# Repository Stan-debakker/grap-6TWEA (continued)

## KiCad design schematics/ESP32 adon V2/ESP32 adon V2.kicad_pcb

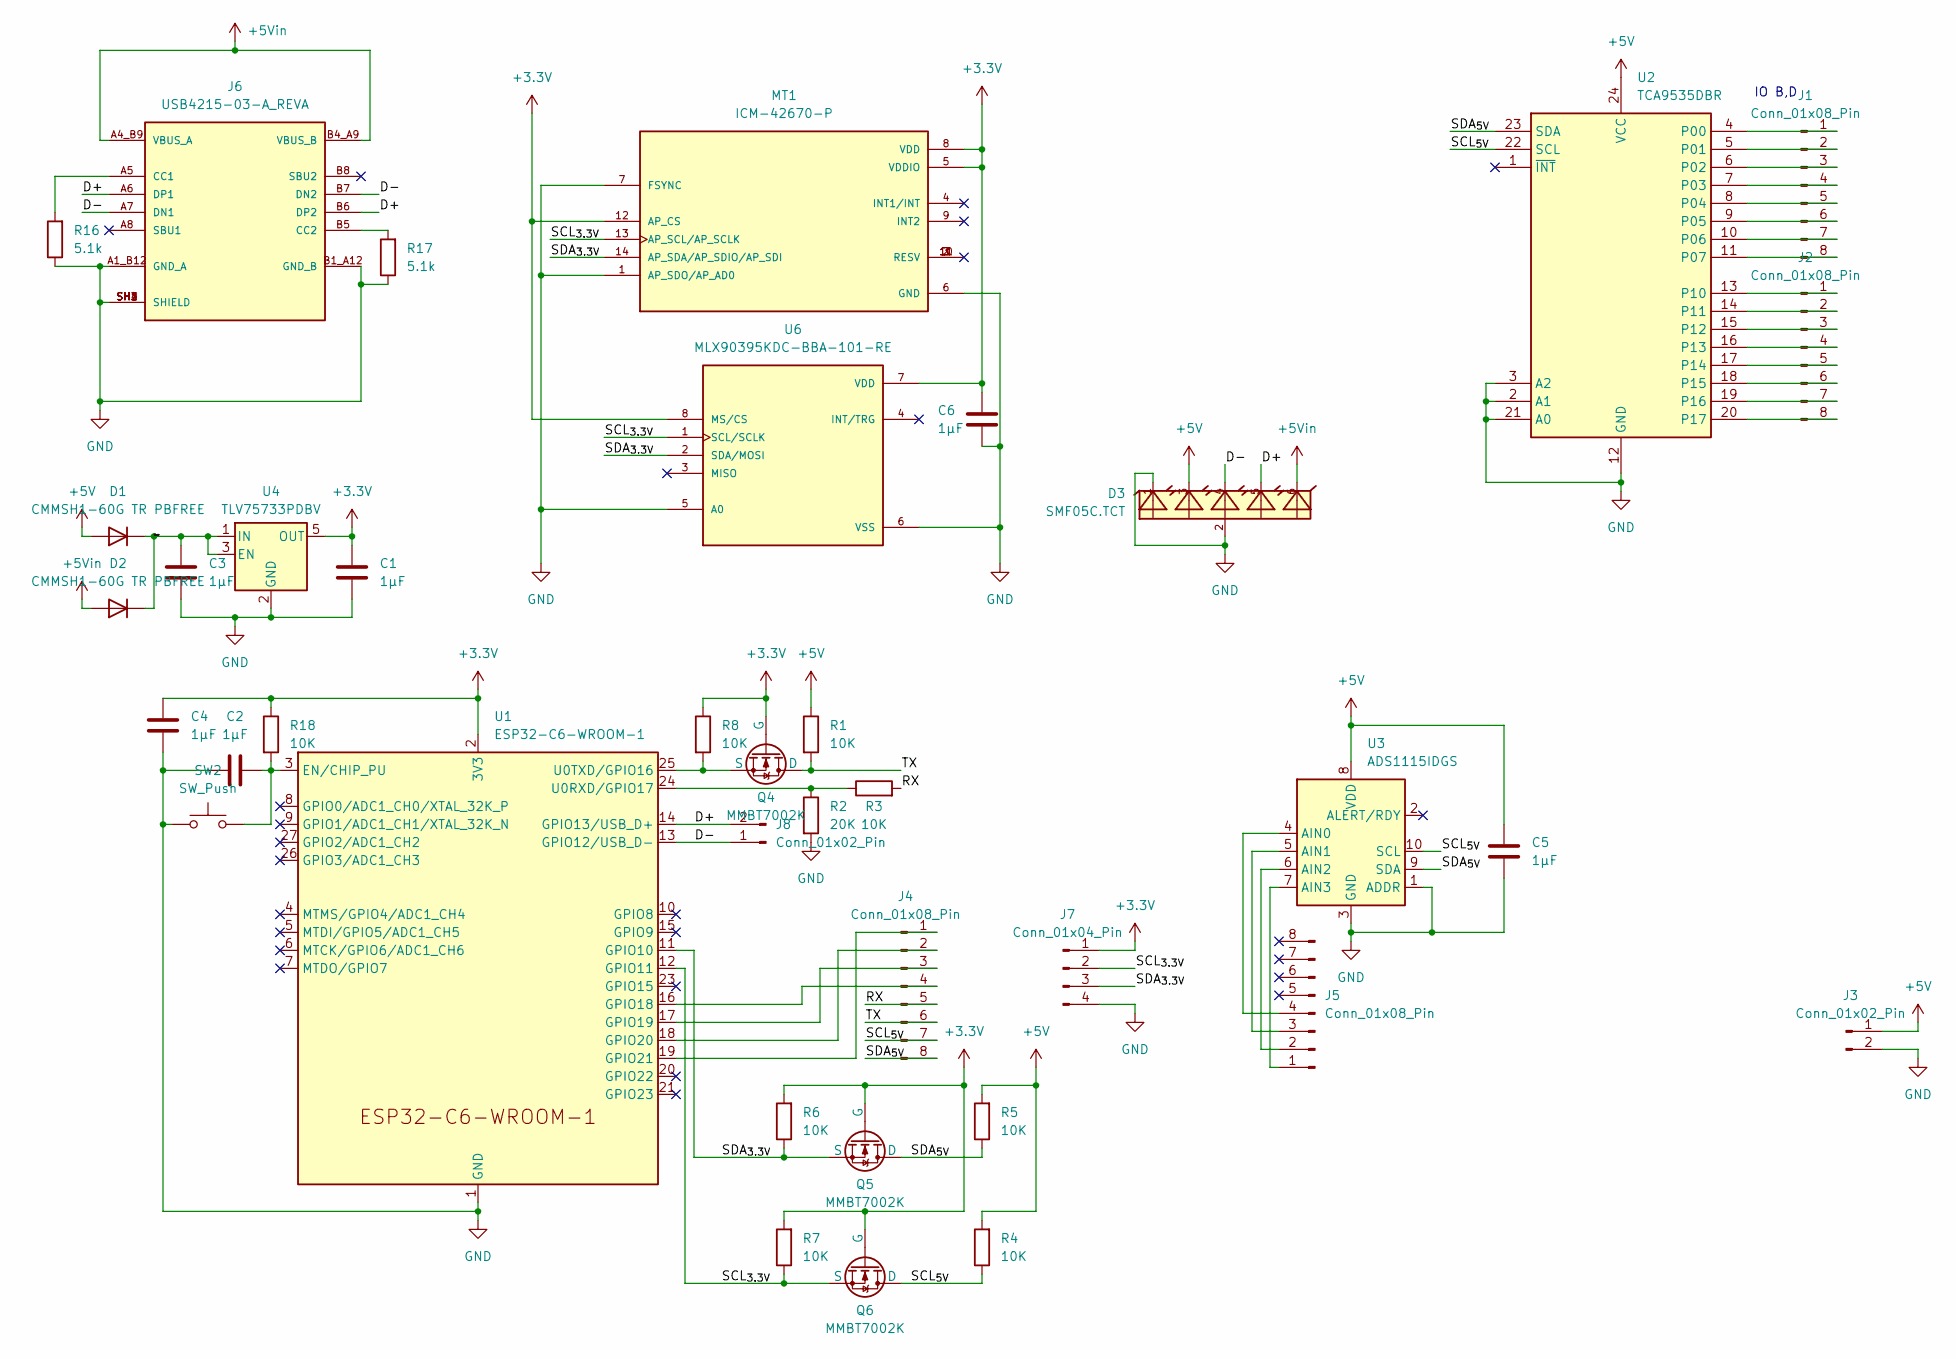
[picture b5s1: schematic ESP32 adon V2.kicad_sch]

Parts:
C1, C2, C3, C4, C5, C6: 1µF; C_0603_1608Metric
D1, D2: CMMSH1-60G TR PBFREE; D_SOD-123F
D3: SMF05C.TCT; Vishay_PowerPAK_SC70-6L_Dual
J1, J2, J4, J5: Conn_01x08_Pin; PinSocket_1x08_P2.54mm_Vertical
J3: Conn_01x02_Pin; PinSocket_1x02_P2.54mm_Vertical
J6: USB4215-03-A_REVA; usb4215-3472997; PARTREV A
J7: Conn_01x04_Pin; PinSocket_1x04_P2.54mm_Vertical
J8: Conn_01x02_Pin; R_0603_1608Metric_Pad0.98x0.95mm_HandSolder
MT1: ICM-42670-P; Bosch_LGA-14_3x2.5mm_P0.5mm; PARTREV 1.1
Q4, Q5, Q6: MMBT7002K; SOT-23
R1, R3, R4, R5, R6, R7, R8, R18: 10K; R_0603_1608Metric
R2: 20K; R_0603_1608Metric
R16, R17: 5.1k; R_0603_1608Metric
SW2: SW_Push; SW_PUSH_6mm
U1: ESP32-C6-WROOM-1
U2: TCA9535DBR; TSSOP-24_4.4x7.8mm_P0.65mm
U3: ADS1115IDGS; TSSOP-10_3x3mm_P0.5mm
U4: TLV75733PDBV; SOT-23-5
U6: MLX90395KDC-BBA-101-RE; SOIC-8_3.9x4.9mm_P1.27mm; PARTREV 6.0

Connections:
+3.3V: C1.1, C4.2, C6.2, J7.1, MT1.5 (VDDIO), MT1.8 (VDD), MT1.12 (AP_CS), Q4.2 (G), Q5.2 (G), Q6.2 (G), R6.2, R7.2, R8.1, R18.1, U1.2 (3V3), U4.5 (OUT), U6.7 (VDD), U6.8 (MS/CS)
+5V: C5.2, D1.2 (A), D3.3, J3.1, R1.1, R4.2, R5.2, U2.24 (VCC), U3.8 (VDD)
+5Vin: D2.2 (A), D3.6, J6.A4_B9 (VBUS_A), J6.B4_A9 (VBUS_B)
/D+: D3.5, J6.A6 (DP1), J6.B6 (DP2), J8.2, U1.14 (GPIO13/USB_D+)
/D-: D3.4, J6.A7 (DN1), J6.B7 (DN2), J8.1, U1.13 (GPIO12/USB_D-)
/RX: J4.5, R3.2
/SCL_{3.3V}: J7.2, MT1.13 (AP_SCL/AP_SCLK), Q6.3 (S), R7.1, U1.12 (GPIO11), U6.1 (SCL/SCLK)
/SCL_{5V}: J4.7, Q6.1 (D), R4.1, U2.22 (SCL), U3.10 (SCL)
/SDA_{3.3V}: J7.3, MT1.14 (AP_SDA/AP_SDIO/AP_SDI), Q5.3 (S), R6.1, U1.11 (GPIO10), U6.2 (SDA/MOSI)
/SDA_{5V}: J4.8, Q5.1 (D), R5.1, U2.23 (SDA), U3.9 (SDA)
/TX: J4.6, Q4.1 (D), R1.2
/Vin_reg: C3.1, D1.1 (K), D2.1 (K), U4.1 (IN), U4.3 (EN)
unnamed: J1.1, U2.4 (P00)
unnamed: J1.2, U2.5 (P01)
unnamed: J1.3, U2.6 (P02)
unnamed: J1.4, U2.7 (P03)
unnamed: J1.5, U2.8 (P04)
unnamed: J1.6, U2.9 (P05)
unnamed: J1.7, U2.10 (P06)
unnamed: J1.8, U2.11 (P07)
unnamed: J2.1, U2.13 (P10)
unnamed: J2.2, U2.14 (P11)
unnamed: J2.3, U2.15 (P12)
unnamed: J2.4, U2.16 (P13)
unnamed: J2.5, U2.17 (P14)
unnamed: J2.6, U2.18 (P15)
unnamed: J2.7, U2.19 (P16)
unnamed: J2.8, U2.20 (P17)
unnamed: J4.1, U1.19 (GPIO21)
unnamed: J4.2, U1.18 (GPIO20)
unnamed: J4.3, U1.17 (GPIO19)
unnamed: J4.4, U1.16 (GPIO18)
unnamed: J5.1, U3.7 (AIN3)
unnamed: J5.2, U3.6 (AIN2)
unnamed: J5.3, U3.5 (AIN1)
unnamed: J5.4, U3.4 (AIN0)
unnamed: J6.A5 (CC1), R16.2
unnamed: J6.B5 (CC2), R17.2
unnamed: Q4.3 (S), R8.2, U1.25 (U0TXD/GPIO16)
unnamed: C2.2, R18.2, SW2.2, U1.3 (EN/CHIP_PU)
unnamed: R2.1, R3.1, U1.24 (U0RXD/GPIO17)

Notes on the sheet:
IO B,D

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
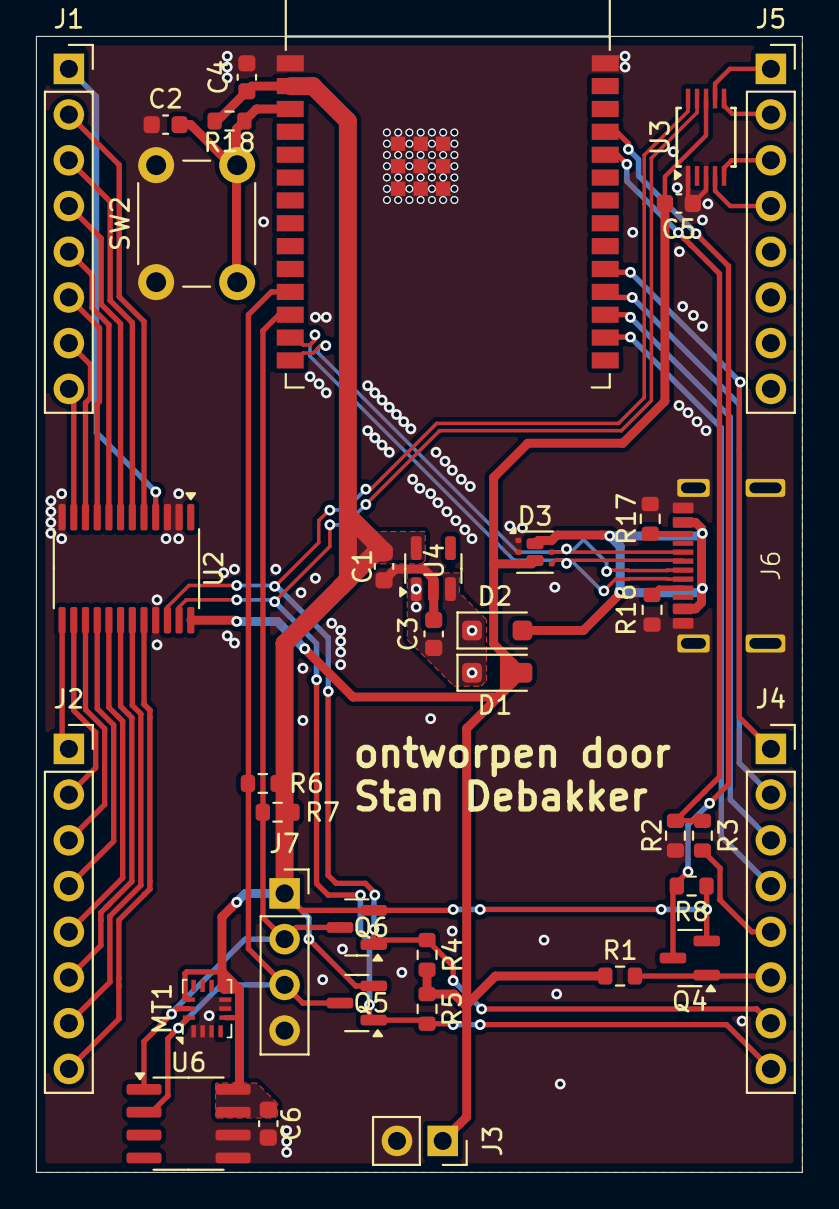
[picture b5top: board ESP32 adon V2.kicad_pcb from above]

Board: 2 copper layers, 42.5 x 63.1 mm, 38 parts (1 on the bottom side), 42 nets.

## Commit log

2025-03-07 voeg de al gemaakte bestanden toe
2025-03-08 verbeterde pcb layout
2025-03-08 voeg de berekeningen toe voor de VIA's
2025-03-08 voeg de voor school verplichte opdrachten toe
2025-03-08 voeg de foto en code om die beter te maken toe
2025-03-08 bug uit code gehaald waardoor het niet update
2025-03-09 kleine update afische
2025-03-09 voeg de word versie van studie 2 toe
2025-03-09 verander de naam van studie_1.pdf naar studie 1.pdf
2025-03-10 voeg de versie volgens mijn mama toe
2025-03-10 afische verbeterd
2025-03-10 de bijna defenitieve versie van de robot
2025-03-10 de finale versie van het afiche
2025-03-11 voeg de exel voor de taak 50% toe
2025-03-11 bijna alle vragen van de taak 50% zijn ingevuld
2025-03-12 voeg de STM32 cubeIDE bestanden (onafgewerkt) toe
2025-03-12 kleine aanpasing om op een arduino Mega te werken
2025-03-12 nutteloze map verwijderd
2025-03-12 voeg .metadata/ toe aan .gitignore om hem niet opte slaan
2025-03-13 update het afiche met de comentaar die ik kreeg
2025-03-13 kleine update van lijnsensor schema
2025-03-17 schema geupdate voor ATtiny 202 (nog niet af)
2025-03-17 schema bijna klaar allen nog SRF02 toevoegen
2025-03-18 wek '50%' voledig af
2025-03-18 hoofdschema is af
2025-03-18 veranert de ATtiny202 naat ATtiny402 om genoeg opslag te hebben
2025-03-18 verwijder code_STM32_cubeIDE omdat ik geen STM32 meer ga gebruiken wan de app deet te ambetand en ik hem niet strict nodig hebben
2025-03-18 voeg de lichtsensor toe aan het hoofd
2025-03-18 .gitignore geupdate zodat de 'nutteloze' bestanden niet worden opgeladen
2025-03-20 teken de outline van het hoofd, en plaats de SRF02 (locatie gevoelig)
2025-03-20 teken de outline van lijnsensor bord + conector positionering
2025-03-21 plaats de componenten grofweg
2025-03-21 voeg de ontbrekende foodprints toe
2025-03-21 teken alles waarvan ik de locate ken of niet belangrijk is (absolut)
2025-03-21 led van het 'mondje' zijn geplaatst
2025-03-21 de locatie van alle componenten is bepaald in het hoofd
2025-03-22 nieuw hoofd is klaar
2025-03-22 ESD bescherming voor de lijnsensor
2025-03-23 de routing is klaar van de lijnsensor nog allen opschonen
2025-03-23 lijnsensor is klaar
2025-03-23 voeg de gaten toe om te kunnen vastvijzen
2025-03-23 maak de gbr file's voor nieuw hoofd
2025-03-23 maak de gbr file's voor lijnsensor
2025-03-23 maak de gbr file's voor ESP32 adon V2
2025-03-29 niewe code voor de ADC geschreven
2025-04-12 voeg todo.txt toe
2025-04-14 IMU.ino en machnetometer.ino werken
2025-04-22 dupliceer de huidige bestanden en voeg de pullup weerstand toe
2025-04-22 verwijder de *.zip bestanden
2025-04-22 update de schematics
2025-04-22 teken al een deel van de lijnsensor
2025-04-24 begin al met het tekenen van ESP32 addon V3
2025-04-24 verder tekenen en datasheets controleren
2025-04-26 voeg de imu en de 3.3V I²C conectoren toe
2025-04-26 zet alle componenten op de juist plaats en alles is al verbonden
2025-04-26 heatsikn voor de ESP32 maken
2025-04-26 voeg het exel document toe waar de via's moeten komen
2025-04-27 controller ESP32 addon V3
2025-04-28 maak een pdf om aftedrukken om te weten als alles goed is
2025-04-28 zet alles op de juiste plaats
2025-04-28 updata alle afmetingen en maak er een pdf van
2025-04-28 teken al wat van het nieuw hoofd
2025-04-29 zet de leds en lichtsensoren op de juisteplaats nieuw hoofd V2
2025-04-29 nieuw hoofd V2 is klaar
2025-04-29 voeg meer via's toe
2025-05-01 klaar met lijnsensor V2
2025-05-01 voeg mijn naam toe aan nieuw hoofd en lijnsensor
2025-05-02 update de .gitignore en voeg viea's toe aan ESP32 addon V3
2025-05-02 verander het I²C adders van de I²C multiplexer om conflict te vermijden
2025-05-02 maak een versie van de lijnsensor die alle pinnen van de lichtsenser gebruikt
2025-05-04 begin al met het toevoegen van de io extender nog niet klaar
2025-05-05 pas de maten aan van de addon V3 en de lijnsensor(nog niet klaar)
2025-05-05 voeg 75%.xlsx toe en vul het al gedeeltelijk in
2025-05-05 de linker kant is al klaar nu nog de rechter kant van lijnsensor V2 met IO_expander
2025-05-05 al begonnen aan de rechterkand van lijnsensor V2 met IO_expander
2025-05-05 klaar met het tekenen van alle verbindingen en veel via's geplaatst
2025-05-06 alles is nagemeten en 75% is ingeleverd
2025-05-06 maak de .gbr bestanden
2025-05-07 maak nieuw hoofd maar met een andere sensorn want de originele is niet meer beschikbaar in kleine hoeveeldheden
2025-05-08 voeg nog ESD bescherming toe aan nieuw hoofd V3
2025-05-09 zorg dat de .gbr files van nieuw hoofd V3 juist zijn
2025-05-11 maak de basis van de eindprisentatie
2025-05-13 voeg iets toe aan todo.txt
2025-05-13 de f.paste layer is goed
2025-05-13 verwijder de oude bestanden van ESP32 adon V4
2025-05-13 verbeter de bibliotheek
2025-05-13 voeg de code voor de IO expander en ADC toe aan de bibliotheek
2025-05-16 de bibliotheek werkt maar IMU en machnetomerter zitten er nog niet in
2025-05-16 voeg de IMU toe aan de liberary
2025-05-16 voeg de machnetometer toe aan de liberary
2025-05-20 maak de code voor de AS7343
2025-05-20 maak de code voor het hoofd
2025-05-20 verder gewerkt aan de powerpoint
2025-05-21 verder gewerkt aan powerpoint
2025-05-22 maak de code voor de lijnsensor
2025-05-25 update de ESP addon en de powerpoint
2025-05-26 verander de io expander op de lijnsensor
2025-05-26 werk verder aan de liberary
2025-06-10 git push wou niet werken
